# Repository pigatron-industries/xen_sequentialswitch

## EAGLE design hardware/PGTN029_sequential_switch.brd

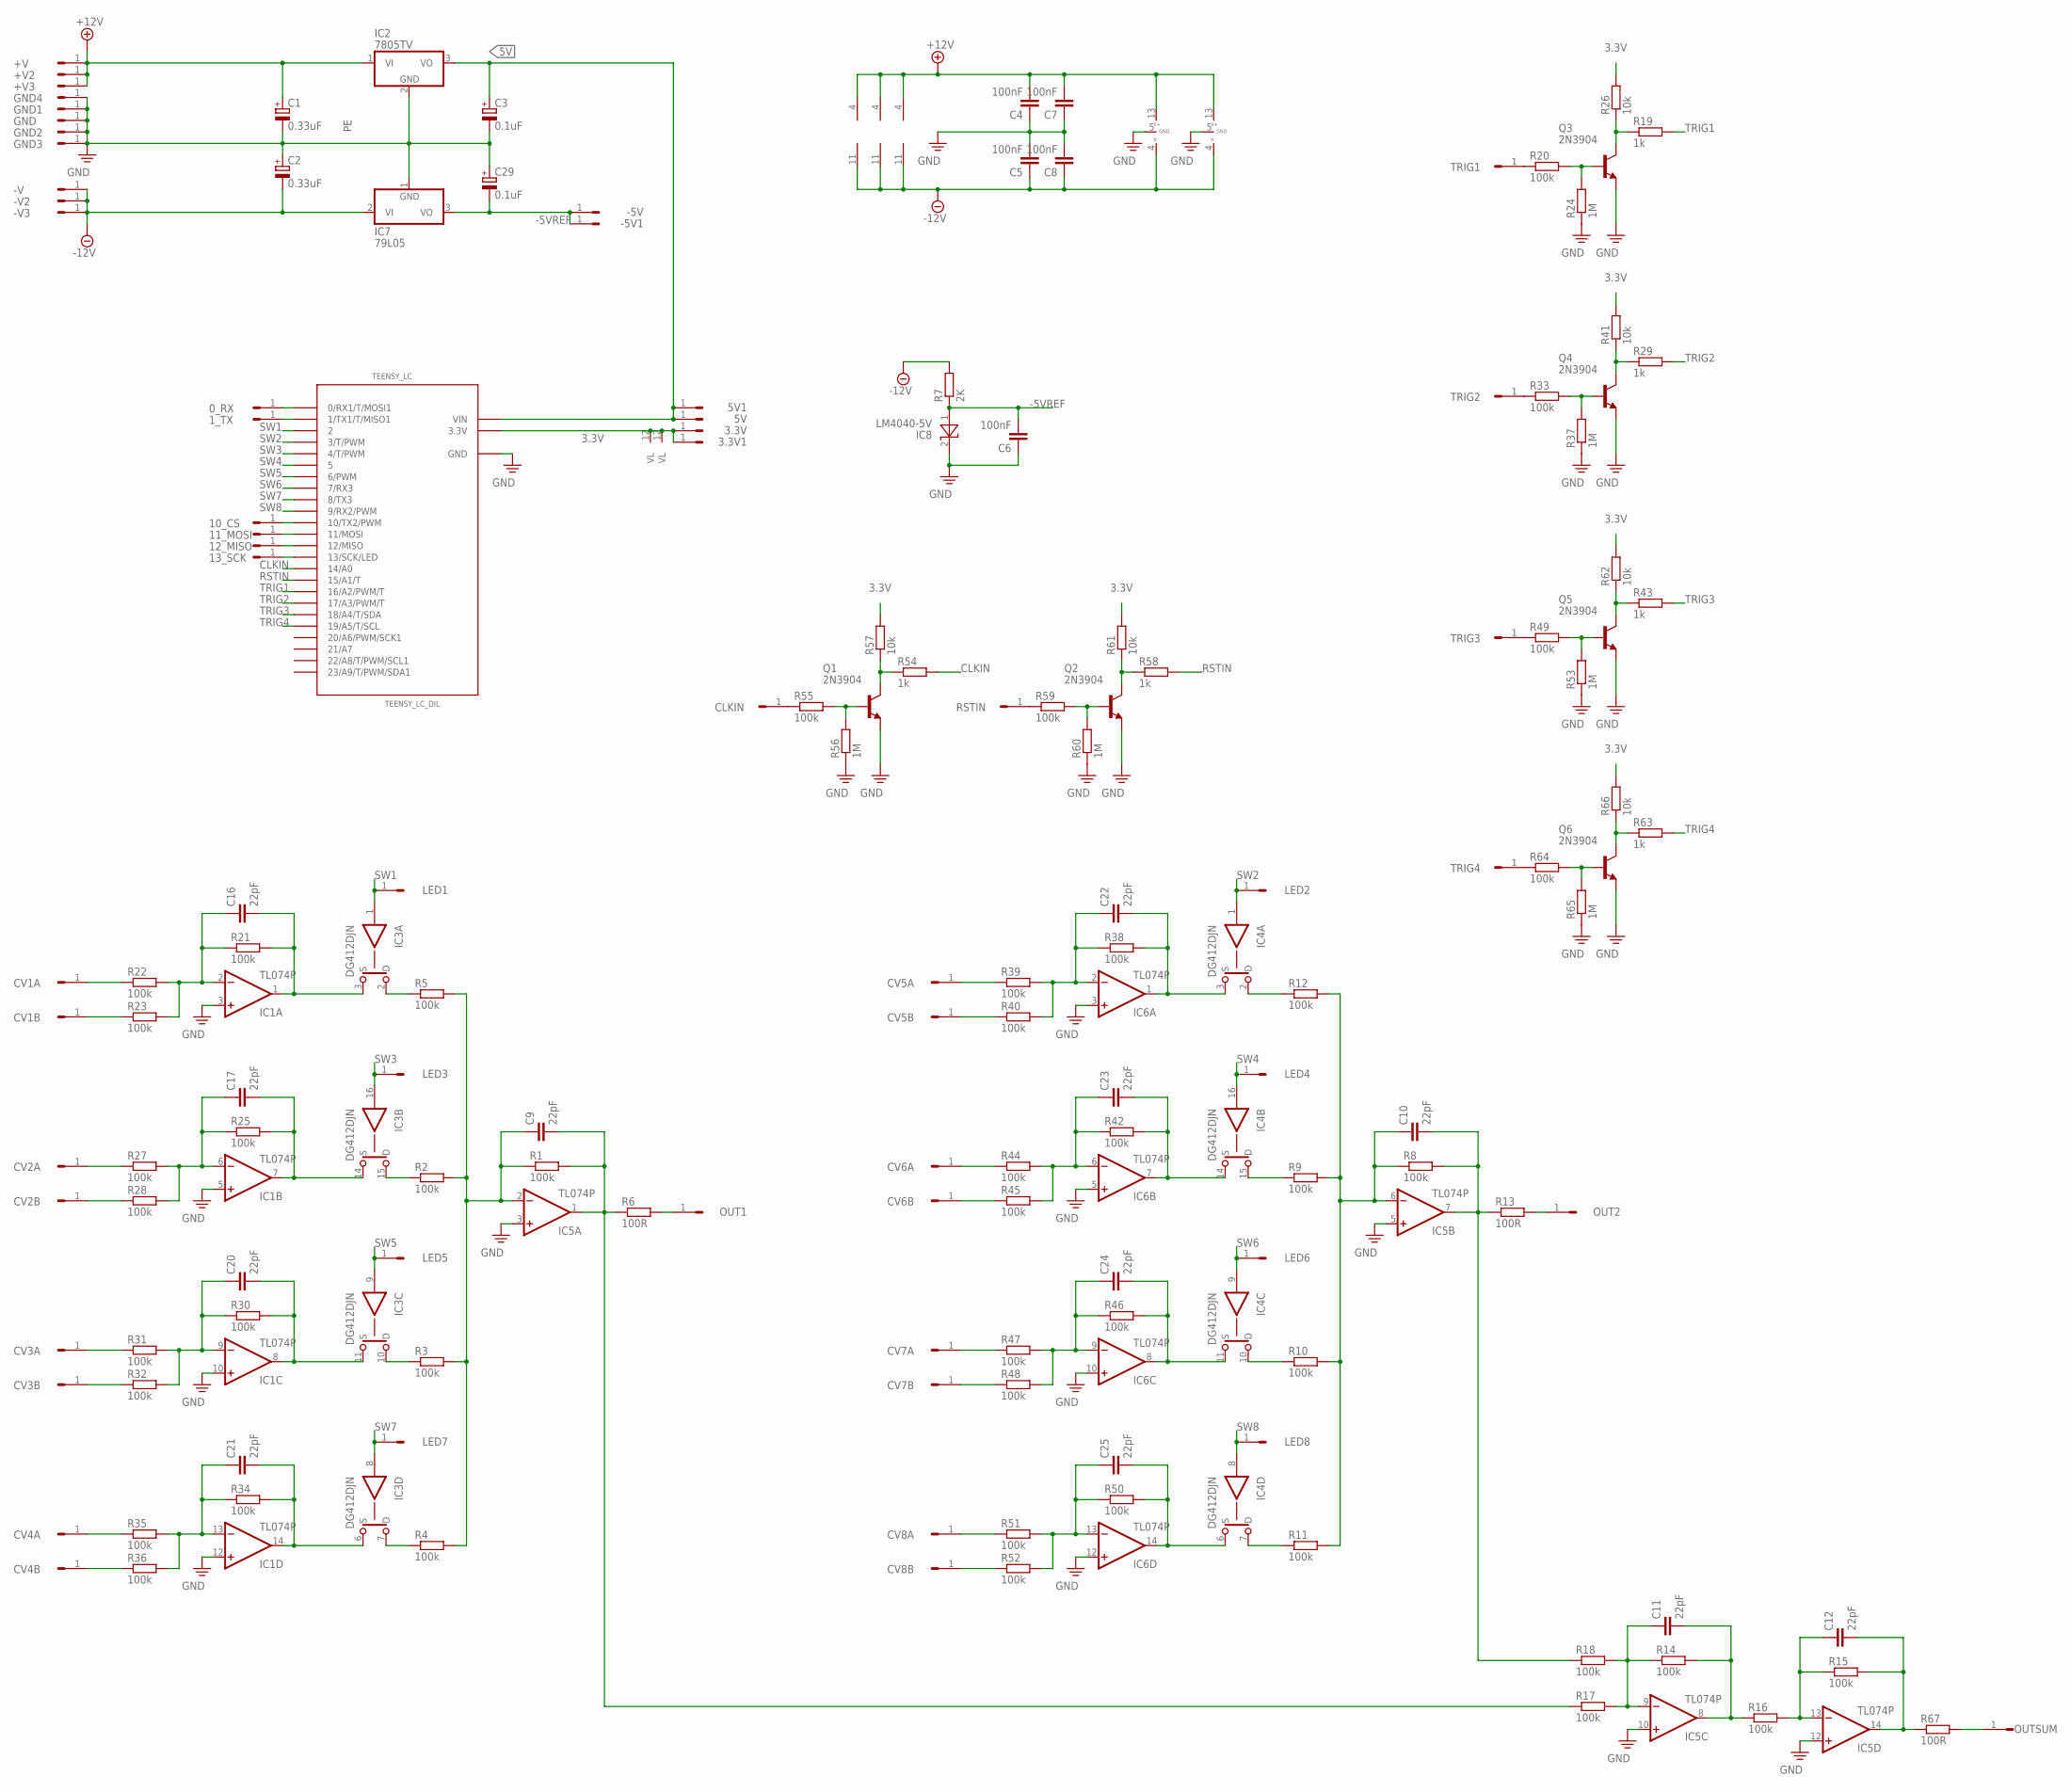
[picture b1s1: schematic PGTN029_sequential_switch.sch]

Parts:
0_RX, 1_TX, 3.3V, 3.3V1, 5V, 5V1, 10_CS, 11_MOSI, 12_MISO, 13_SCK: HEADER/MALE/01
+V, +V2, +V3: HEADER/MALE/01
-5V, -5V1: HEADER/MALE/01
-V, -V2, -V3: HEADER/MALE/01
C1, C2: 0.33uF; E2,5-6
C3, C29: 0.1uF; E2,5-6
C4, C5, C6, C7, C8: 100nF; CERAMICDISC/5
C9, C10, C11, C12, C16, C17, C20, C21, C22, C23, C24, C25: 22pF; CERAMICDISC/5
CLKIN: HEADER/MALE/01
CV1A, CV1B, CV2A, CV2B, CV3A, CV3B, CV4A, CV4B, CV5A, CV5B, CV6A, CV6B, CV7A, CV7B, CV8A, CV8B: HEADER/MALE/01
GND, GND1, GND2, GND3, GND4: HEADER/MALE/01
IC1, IC5, IC6: TL074P; DIL14
IC2: 7805TV; TO220V
IC3, IC4: DG412DJN; DIL16
IC7: 79L05; TO92
IC8: LM4040-5V; TO92
LED1, LED2, LED3, LED4, LED5, LED6, LED7, LED8: HEADER/MALE/01
OUT1, OUT2: HEADER/MALE/01
OUTSUM: HEADER/MALE/01
Q1, Q2, Q3, Q4, Q5, Q6: 2N3904; TO92
R1, R2, R3, R4, R5, R8, R9, R10, R11, R12, R14, R15, R16, R17, R18, R20, R21, R22, R23, R25, R27, R28, R30, R31, R32, R33, R34, R35, R36, R38, R39, R40, R42, R44, R45, R46, R47, R48, R49, R50, R51, R52, R55, R59, R64: 100k; RESISTOR/7.5
R6, R13, R67: 100R; RESISTOR/7.5
R7: 2K; RESISTOR/7.5
R19, R29, R43, R54, R58, R63: 1k; RESISTOR/7.5
R24, R37, R53, R56, R60, R65: 1M; RESISTOR/7.5
R26, R41, R57, R61, R62, R66: 10k; RESISTOR/7.5
RSTIN: HEADER/MALE/01
TEENSY_LC: TEENSY_LC_DIL; TEENSY_3.0-3.2&LC_DIL
TRIG1, TRIG2, TRIG3, TRIG4: HEADER/MALE/01

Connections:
3.3V: 3.3V.1, 3.3V1.1, IC3.12 (VL), IC4.12 (VL), R26.2, R41.2, R57.2, R61.2, R62.2, R66.2, TEENSY_LC.3.3V
5V: 5V.1, 5V1.1, C3.+, IC2.3 (VO), TEENSY_LC.VIN
+12V: +V.1, +V2.1, +V3.1, C1.+, C4.2, C7.2, IC1.4 (V+), IC2.1 (VI), IC3.13 (V+), IC4.13 (V+), IC5.4 (V+), IC6.4 (V+)
-5VREF: -5V.1, -5V1.1, C6.2, C29.-, IC7.3 (VO), IC8.1 (A), R7.1
-12V: -V.1, -V2.1, -V3.1, C2.-, C5.1, C8.1, IC1.11 (V-), IC3.4 (V-), IC4.4 (V-), IC5.11 (V-), IC6.11 (V-), IC7.2 (VI), R7.2
ADC0: C16.2, IC1.1 (OUT), IC3.3 (S), R21.2
ADC1: C17.2, IC1.7 (OUT), IC3.14 (S), R25.2
ADC2: C20.2, IC1.8 (OUT), IC3.11 (S), R30.2
ADC3: C21.2, IC1.14 (OUT), IC3.6 (S), R34.2
ADC4: C22.2, IC4.3 (S), IC6.1 (OUT), R38.2
ADC5: C23.2, IC4.14 (S), IC6.7 (OUT), R42.2
ADC6: C24.2, IC4.11 (S), IC6.8 (OUT), R46.2
ADC7: C25.2, IC4.6 (S), IC6.14 (OUT), R50.2
CLKIN: R54.2, TEENSY_LC.14/A0
unnamed: CV2A.1, R27.1
unnamed: C9.1, IC5.2 (-IN), R1.1, R2.2, R3.2, R4.2, R5.2
unnamed: C9.2, IC5.1 (OUT), R1.2, R6.1, R17.1
unnamed: IC3.15 (D), R2.1
unnamed: IC3.2 (D), R5.1
unnamed: IC3.10 (D), R3.1
unnamed: IC3.7 (D), R4.1
unnamed: C10.1, IC5.6 (-IN), R8.1, R9.2, R10.2, R11.2, R12.2
unnamed: C10.2, IC5.7 (OUT), R8.2, R13.1, R18.1
unnamed: IC4.15 (D), R9.1
unnamed: IC4.2 (D), R12.1
unnamed: IC4.10 (D), R10.1
unnamed: IC4.7 (D), R11.1
unnamed: OUT1.1, R6.2
unnamed: OUT2.1, R13.2
unnamed: C11.2, IC5.8 (OUT), R14.2, R16.1
unnamed: C11.1, IC5.9 (-IN), R14.1, R17.2, R18.2
unnamed: C12.2, IC5.14 (OUT), R15.2, R67.1
unnamed: C12.1, IC5.13 (-IN), R15.1, R16.2
unnamed: R20.1, TRIG1.1
unnamed: Q3.2 (B), R20.2, R24.2
unnamed: CV1A.1, R22.1
unnamed: Q3.1 (C), R19.1, R26.1
unnamed: C16.1, IC1.2 (-IN), R21.1, R22.2, R23.2
unnamed: R59.1, RSTIN.1
unnamed: CV2B.1, R28.1
unnamed: CV1B.1, R23.1
unnamed: OUTSUM.1, R67.2
unnamed: C17.1, IC1.6 (-IN), R25.1, R27.2, R28.2
unnamed: C21.1, IC1.13 (-IN), R34.1, R35.2, R36.2
unnamed: CV4A.1, R35.1
unnamed: CV4B.1, R36.1
unnamed: R33.1, TRIG2.1
unnamed: CV3B.1, R32.1
unnamed: CV3A.1, R31.1
unnamed: C20.1, IC1.9 (-IN), R30.1, R31.2, R32.2
unnamed: 12_MISO.1, TEENSY_LC.12 (12/MISO)
unnamed: C22.1, IC6.2 (-IN), R38.1, R39.2, R40.2
unnamed: 0_RX.1, TEENSY_LC.0 (0/RX1/T/MOSI1)
unnamed: CV5B.1, R40.1
unnamed: CV5A.1, R39.1
unnamed: 1_TX.1, TEENSY_LC.1 (1/TX1/T/MISO1)
unnamed: C23.1, IC6.6 (-IN), R42.1, R44.2, R45.2
unnamed: CV6A.1, R44.1
unnamed: CV6B.1, R45.1
unnamed: C25.1, IC6.13 (-IN), R50.1, R51.2, R52.2
unnamed: Q4.2 (B), R33.2, R37.2
unnamed: CV8A.1, R51.1
unnamed: CV8B.1, R52.1
unnamed: CV7B.1, R48.1
unnamed: CV7A.1, R47.1
unnamed: C24.1, IC6.9 (-IN), R46.1, R47.2, R48.2
unnamed: Q4.1 (C), R29.1, R41.1
unnamed: CLKIN.1, R55.1
unnamed: Q1.2 (B), R55.2, R56.2
unnamed: Q1.1 (C), R54.1, R57.1
unnamed: Q2.2 (B), R59.2, R60.2
unnamed: Q2.1 (C), R58.1, R61.1
unnamed: R49.1, TRIG3.1
unnamed: Q5.2 (B), R49.2, R53.2
unnamed: 10_CS.1, TEENSY_LC.10 (10/TX2/PWM)
unnamed: 11_MOSI.1, TEENSY_LC.11 (11/MOSI)
unnamed: 13_SCK.1, TEENSY_LC.13 (13/SCK/LED)
unnamed: Q5.1 (C), R43.1, R62.1
unnamed: R64.1, TRIG4.1
unnamed: Q6.2 (B), R64.2, R65.2
unnamed: Q6.1 (C), R63.1, R66.1
PE: C1.-, C2.+, C3.-, C4.1, C5.2, C6.1, C7.1, C8.2, C29.+, GND.1, GND1.1, GND2.1, GND3.1, GND4.1, IC1.3 (+IN), IC1.5 (+IN), IC1.10 (+IN), IC1.12 (+IN), IC2.2 (GND), IC3.5 (GND), IC4.5 (GND), IC5.3 (+IN), IC5.5 (+IN), IC5.10 (+IN), IC5.12 (+IN), IC6.3 (+IN), IC6.5 (+IN), IC6.10 (+IN), IC6.12 (+IN), IC7.1 (GND), IC8.2 (C), Q1.3 (E), Q2.3 (E), Q3.3 (E), Q4.3 (E), Q5.3 (E), Q6.3 (E), R24.1, R37.1, R53.1, R56.1, R60.1, R65.1, TEENSY_LC.AGND (GND), TEENSY_LC.GND
RSTIN: R58.2, TEENSY_LC.15/A1 (15/A1/T)
SW1: IC3.1 (IN), LED1.1, TEENSY_LC.2
SW2: IC4.1 (IN), LED2.1, TEENSY_LC.3 (3/T/PWM)
SW3: IC3.16 (IN), LED3.1, TEENSY_LC.4 (4/T/PWM)
SW4: IC4.16 (IN), LED4.1, TEENSY_LC.5
SW5: IC3.9 (IN), LED5.1, TEENSY_LC.6 (6/PWM)
SW6: IC4.9 (IN), LED6.1, TEENSY_LC.7 (7/RX3)
SW7: IC3.8 (IN), LED7.1, TEENSY_LC.8 (8/TX3)
SW8: IC4.8 (IN), LED8.1, TEENSY_LC.9 (9/RX2/PWM)
TRIG1: R19.2, TEENSY_LC.16/A2 (16/A2/PWM/T)
TRIG2: R29.2, TEENSY_LC.17/A3 (17/A3/PWM/T)
TRIG3: R43.2, TEENSY_LC.18/A4 (18/A4/T/SDA)
TRIG4: R63.2, TEENSY_LC.19/A5 (19/A5/T/SCL)

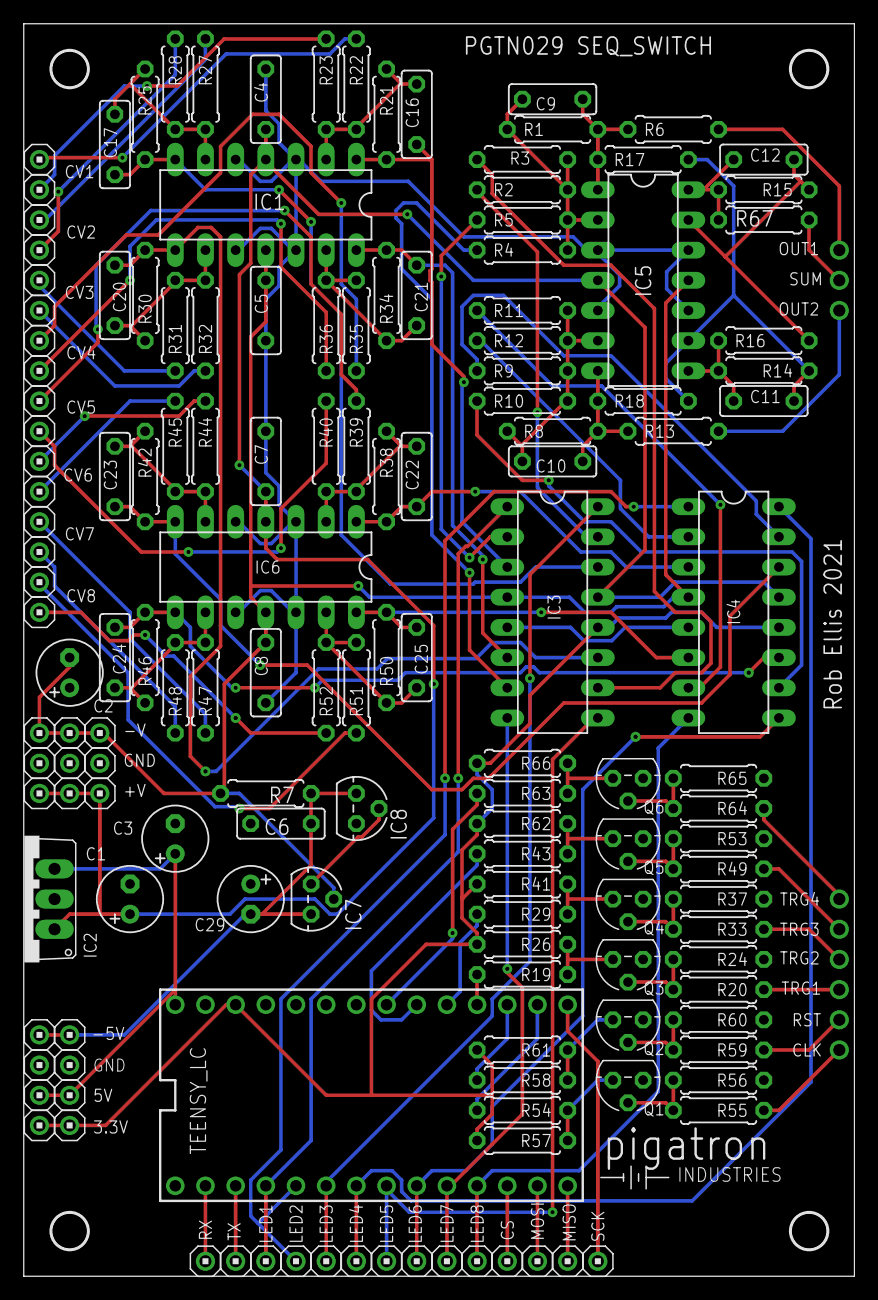
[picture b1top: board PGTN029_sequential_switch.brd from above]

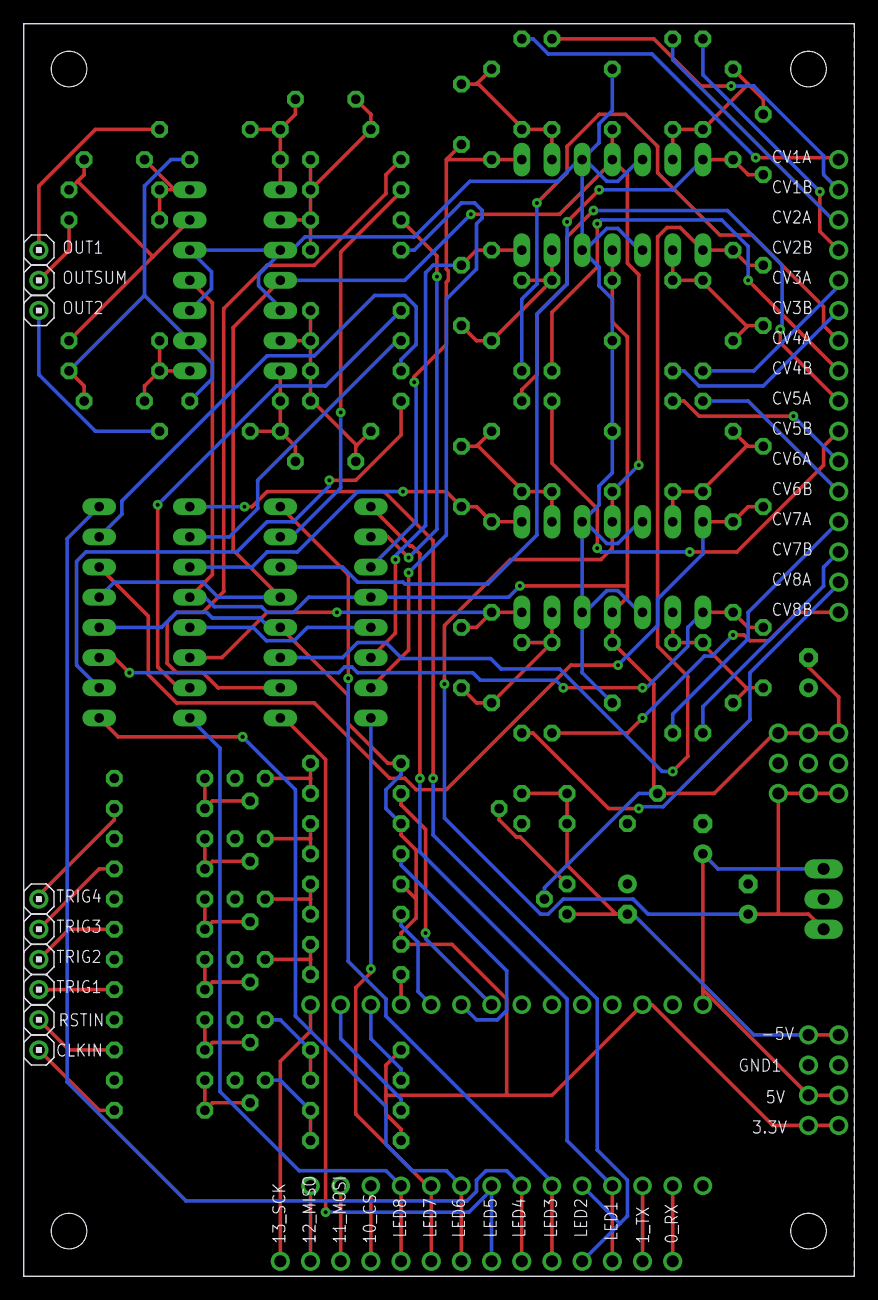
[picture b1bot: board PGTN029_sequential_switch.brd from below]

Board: 2 copper layers, 69.9 x 105.4 mm, 164 parts (9 on the bottom side), 95 nets.

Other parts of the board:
U$2, U$3, U$4, U$7: STANDOFF/3.0
U$5: PIGATRON-LOGO

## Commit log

2021-08-22 template
2021-09-18 Updated lib
